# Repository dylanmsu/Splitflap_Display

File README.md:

# Splitflap_Display
software to digtally drive a public splitflap display using arduino. The display is meant do be deployed in a steamtrain station where it reads the data from their server.
This project is still in development and requires major improvements and code cleanup.

## this repository contains:
* arduino library
* kicad schematic and pcb desgin
* basic documentation about the splitflap display modules

## The Arduino compatible Library
The included Arduino compatible library is designed to drive a complete split flap display board with 32 individual modules. There are also methods included to drive the individual split flaps with great control. You can for example call the method:
```c++
splitflaps.flipSegment(int segment);
```
That line of code will flip the segment once. Or if you want more control, there is the method: 
```c++
splitflaps.writeSegment(int segment, int state);
```
It sets the state of the selected h-Bridge. There are (in the future) a bunch of example sketches with different use cases for the library. However, they all require at least one driver PCB to actually drive the split flap modules.

## The driver PCB
The driver PCBs can drive 8 splitflap modules at the same time, for that it uses 4 SN754410NE chips (L293D in version 4) that are driven by two 74HC595 shift registers. One shift registers drives the H-bridges, the other enables the outputs of the 8 H-Bridges so they dont waste unnecessary power. The communication protocol is quite simple. You have two serial data inputs in the input connector, one is to enable the individual H-Bridges (DiE, ClkE, LaE), the other is to drive the individual H-bridges (Di, Clk, La). They can be daisy-chained to drive an infinite number of splitflap modules. <br> To actually drive splitflap modules with it, open the arduino sketch named TestDriver. Connect the splitflap modules solenoid connections to the H-Bridge output pairs. Then connect the serial pins to the arduino pins listed in the sketch. and lastly connect 20v to the Vdd input connector. Upload the sketch, the splitflaps should be working.

* V1: first version, fully made in kicad with through hole components
* V4: latest version, made in EasyEDA with mostly SMD components

## authors
* Dylan Missuwe
* Tijl Desmet

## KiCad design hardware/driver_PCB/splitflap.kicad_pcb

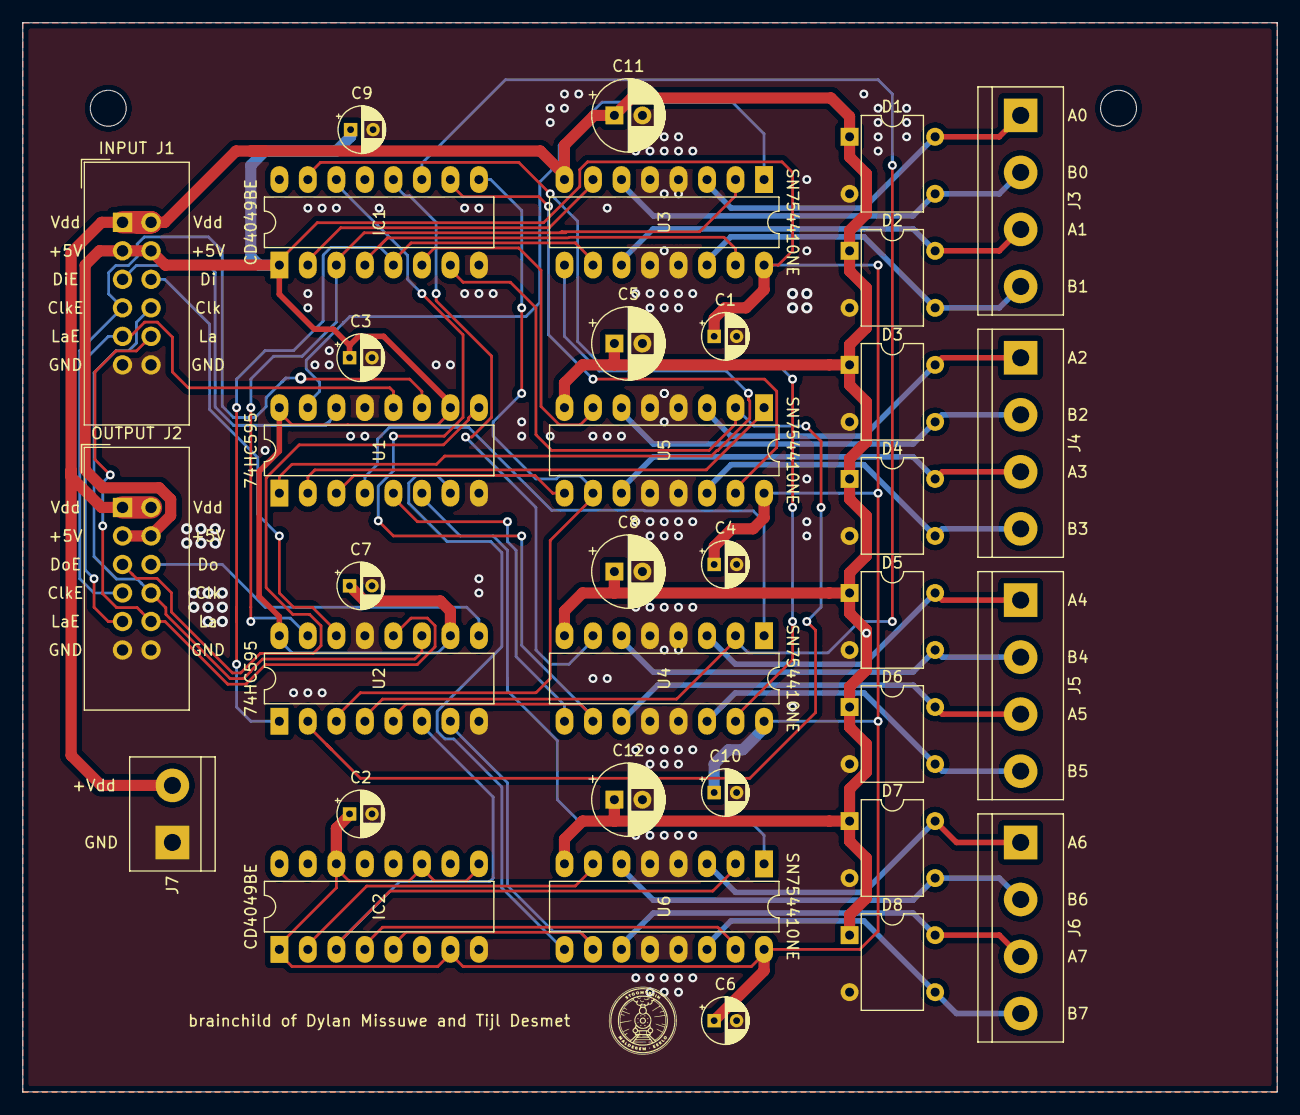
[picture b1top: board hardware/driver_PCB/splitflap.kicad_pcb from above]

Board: 2 copper layers, 111.8 x 95.2 mm, 35 parts (0 on the bottom side), 51 nets.

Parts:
C1, C2, C3, C4, C6, C7, C9, C10: CP; CP_Radial_D4.0mm_P2.00mm
C5, C8, C11, C12: CP; CP_Radial_D6.3mm_P2.50mm
D1, D2, D3, D4, D5, D6, D7, D8: D_Bridge_+-AA; Diode_Bridge_DIP-4_W7.62mm_P5.08mm
IC1, IC2: CD4049UBE; DIP-16_W7.62mm_LongPads
INPUT J1: Conn_02x06_Odd_Even; IDC-Header_2x06_P2.54mm_Vertical
J3, J4, J5, J6: Screw_Terminal_01x04; TerminalBlock_bornier-4_P5.08mm
J7: Screw_Terminal_01x02; TerminalBlock_bornier-2_P5.08mm
OUTPUT J2: Conn_02x06_Odd_Even; IDC-Header_2x06_P2.54mm_Vertical
U1, U2: 74HC595; DIP-16_W7.62mm_LongPads
U3, U4, U5, U6: SN754410NE; DIP-16_W7.62mm_LongPads

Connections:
GND: C1.2, C2.2, C3.2, C4.2, C5.2, C6.2, C7.2, C8.2, C9.2, C10.2, C11.2, C12.2, D1.2, D2.2, D3.2, D4.2, D5.2, D6.2, D7.2, D8.2, IC1.8, IC2.8, INPUT J1.11, INPUT J1.12, J7.1, OUTPUT J2.11, OUTPUT J2.12, U1.8, U1.13, U2.8, U2.13, U3.4, U3.5, U3.12, U3.13, U4.4, U4.5, U4.12, U4.13, U5.4, U5.5, U5.12, U5.13, U6.4, U6.5, U6.12, U6.13
unnamed: D1.3, J3.2, U3.6
unnamed: D1.4, J3.1, U3.3
unnamed: D2.3, J3.4, U3.14
unnamed: D2.4, J3.3, U3.11
unnamed: D3.3, J4.2, U5.6
unnamed: D3.4, J4.1, U5.3
unnamed: D4.3, J4.4, U5.14
unnamed: D4.4, J4.3, U5.11
unnamed: D5.3, J5.2, U4.6
unnamed: D5.4, J5.1, U4.3
unnamed: D6.3, J5.4, U4.14
unnamed: D6.4, J5.3, U4.11
unnamed: D7.3, J6.2, U6.6
unnamed: D7.4, J6.1, U6.3
unnamed: D8.3, J6.4, U6.14
unnamed: D8.4, J6.3, U6.11
unnamed: IC1.2, U3.7
unnamed: IC1.3, U2.15, U3.2
unnamed: IC1.4, U3.15
unnamed: IC1.5, U2.1, U3.10
unnamed: IC1.6, U5.7
unnamed: IC1.7, U2.2, U5.2
unnamed: IC1.9, U2.3, U5.10
unnamed: IC1.10, U5.15
unnamed: IC1.11, U2.4, U4.2
unnamed: IC1.12, U4.7
unnamed: IC1.14, U2.5, U4.10
unnamed: IC1.15, U4.15
unnamed: IC2.2, U6.7
unnamed: IC2.3, U2.6, U6.2
unnamed: IC2.4, U6.15
unnamed: IC2.5, U2.7, U6.10
unnamed: INPUT J1.5, U1.14
unnamed: INPUT J1.6, U2.14
unnamed: INPUT J1.7, OUTPUT J2.7, U1.11
unnamed: INPUT J1.8, OUTPUT J2.8, U2.11
unnamed: INPUT J1.9, OUTPUT J2.9, U1.12
unnamed: INPUT J1.10, OUTPUT J2.10, U2.12
unnamed: OUTPUT J2.5, U1.9
unnamed: OUTPUT J2.6, U2.9
unnamed: U1.1, U3.9
unnamed: U1.2, U5.1
unnamed: U1.3, U5.9
unnamed: U1.4, U4.1
unnamed: U1.5, U4.9
unnamed: U1.6, U6.1
unnamed: U1.7, U6.9
unnamed: U1.15, U3.1
VCC: C1.1, C2.1, C3.1, C4.1, C6.1, C7.1, C9.1, C10.1, IC1.1, IC2.1, IC2.7, IC2.9, IC2.11, IC2.14, INPUT J1.3, INPUT J1.4, OUTPUT J2.3, OUTPUT J2.4, U1.10, U1.16, U2.10, U2.16, U3.16, U4.16, U5.16, U6.16
VDD: C5.1, C8.1, C11.1, C12.1, D1.1, D2.1, D3.1, D4.1, D5.1, D6.1, D7.1, D8.1, INPUT J1.1, INPUT J1.2, J7.2, OUTPUT J2.1, OUTPUT J2.2, U3.8, U4.8, U5.8, U6.8

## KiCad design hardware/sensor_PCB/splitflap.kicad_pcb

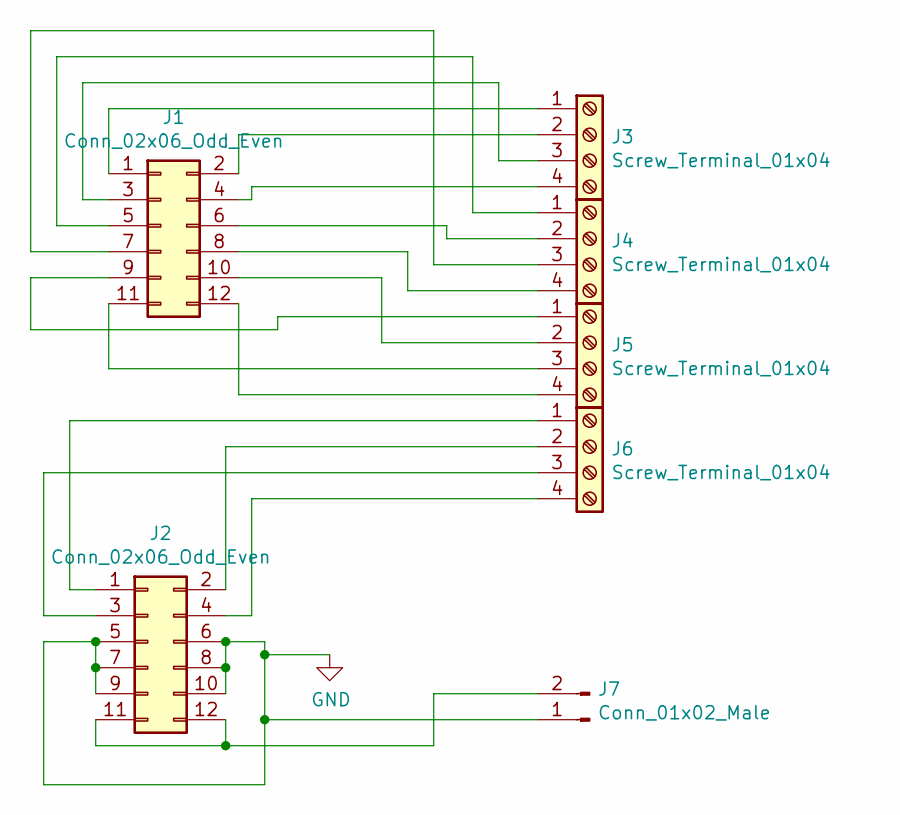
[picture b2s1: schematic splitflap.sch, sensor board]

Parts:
J1, J2: Conn_02x06_Odd_Even; IDC-Header_2x06_P2.54mm_Vertical
J3, J4, J5, J6: Screw_Terminal_01x04; TerminalBlock_bornier-4_P5.08mm
J7: Conn_01x02_Male; JST_EH_B2B-EH-A_1x02_P2.50mm_Vertical

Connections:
GND: J2.5, J2.6, J2.7, J2.8, J2.9, J2.10, J7.1
unnamed: J1.1, J3.1
unnamed: J1.2, J3.2
unnamed: J1.3, J3.3
unnamed: J1.4, J3.4
unnamed: J1.5, J4.1
unnamed: J1.6, J4.2
unnamed: J1.7, J4.3
unnamed: J1.8, J4.4
unnamed: J1.9, J5.1
unnamed: J1.10, J5.2
unnamed: J1.11, J5.3
unnamed: J1.12, J5.4
unnamed: J2.1, J6.1
unnamed: J2.2, J6.2
unnamed: J2.3, J6.3
unnamed: J2.4, J6.4
unnamed: J2.11, J2.12, J7.2

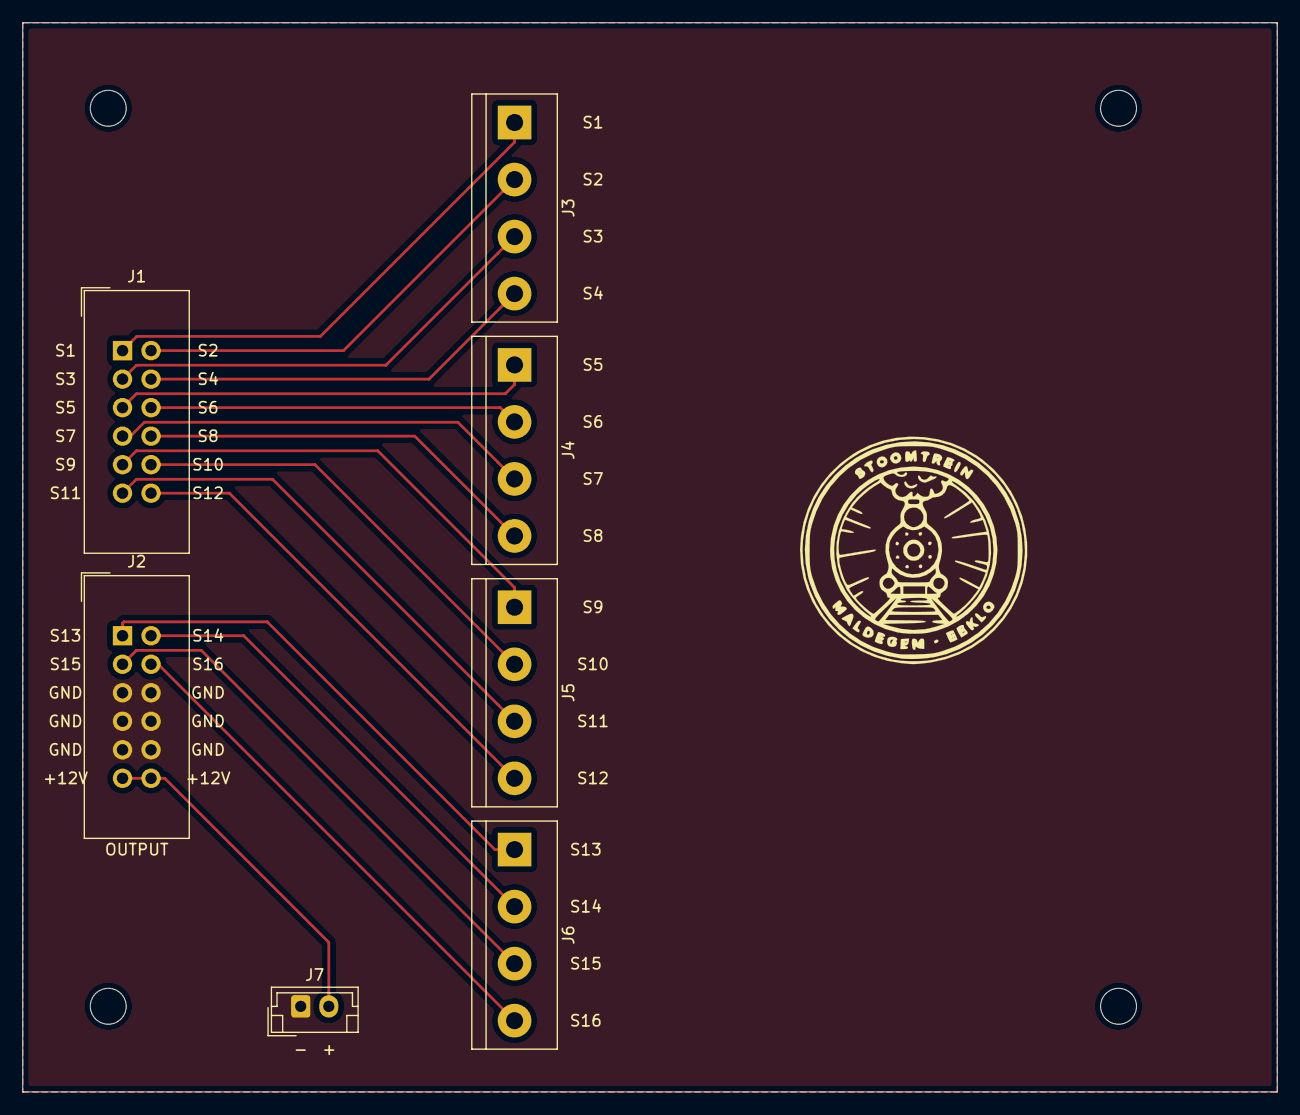
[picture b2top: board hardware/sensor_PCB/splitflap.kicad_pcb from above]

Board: 2 copper layers, 111.8 x 95.2 mm, 7 parts (0 on the bottom side), 18 nets.

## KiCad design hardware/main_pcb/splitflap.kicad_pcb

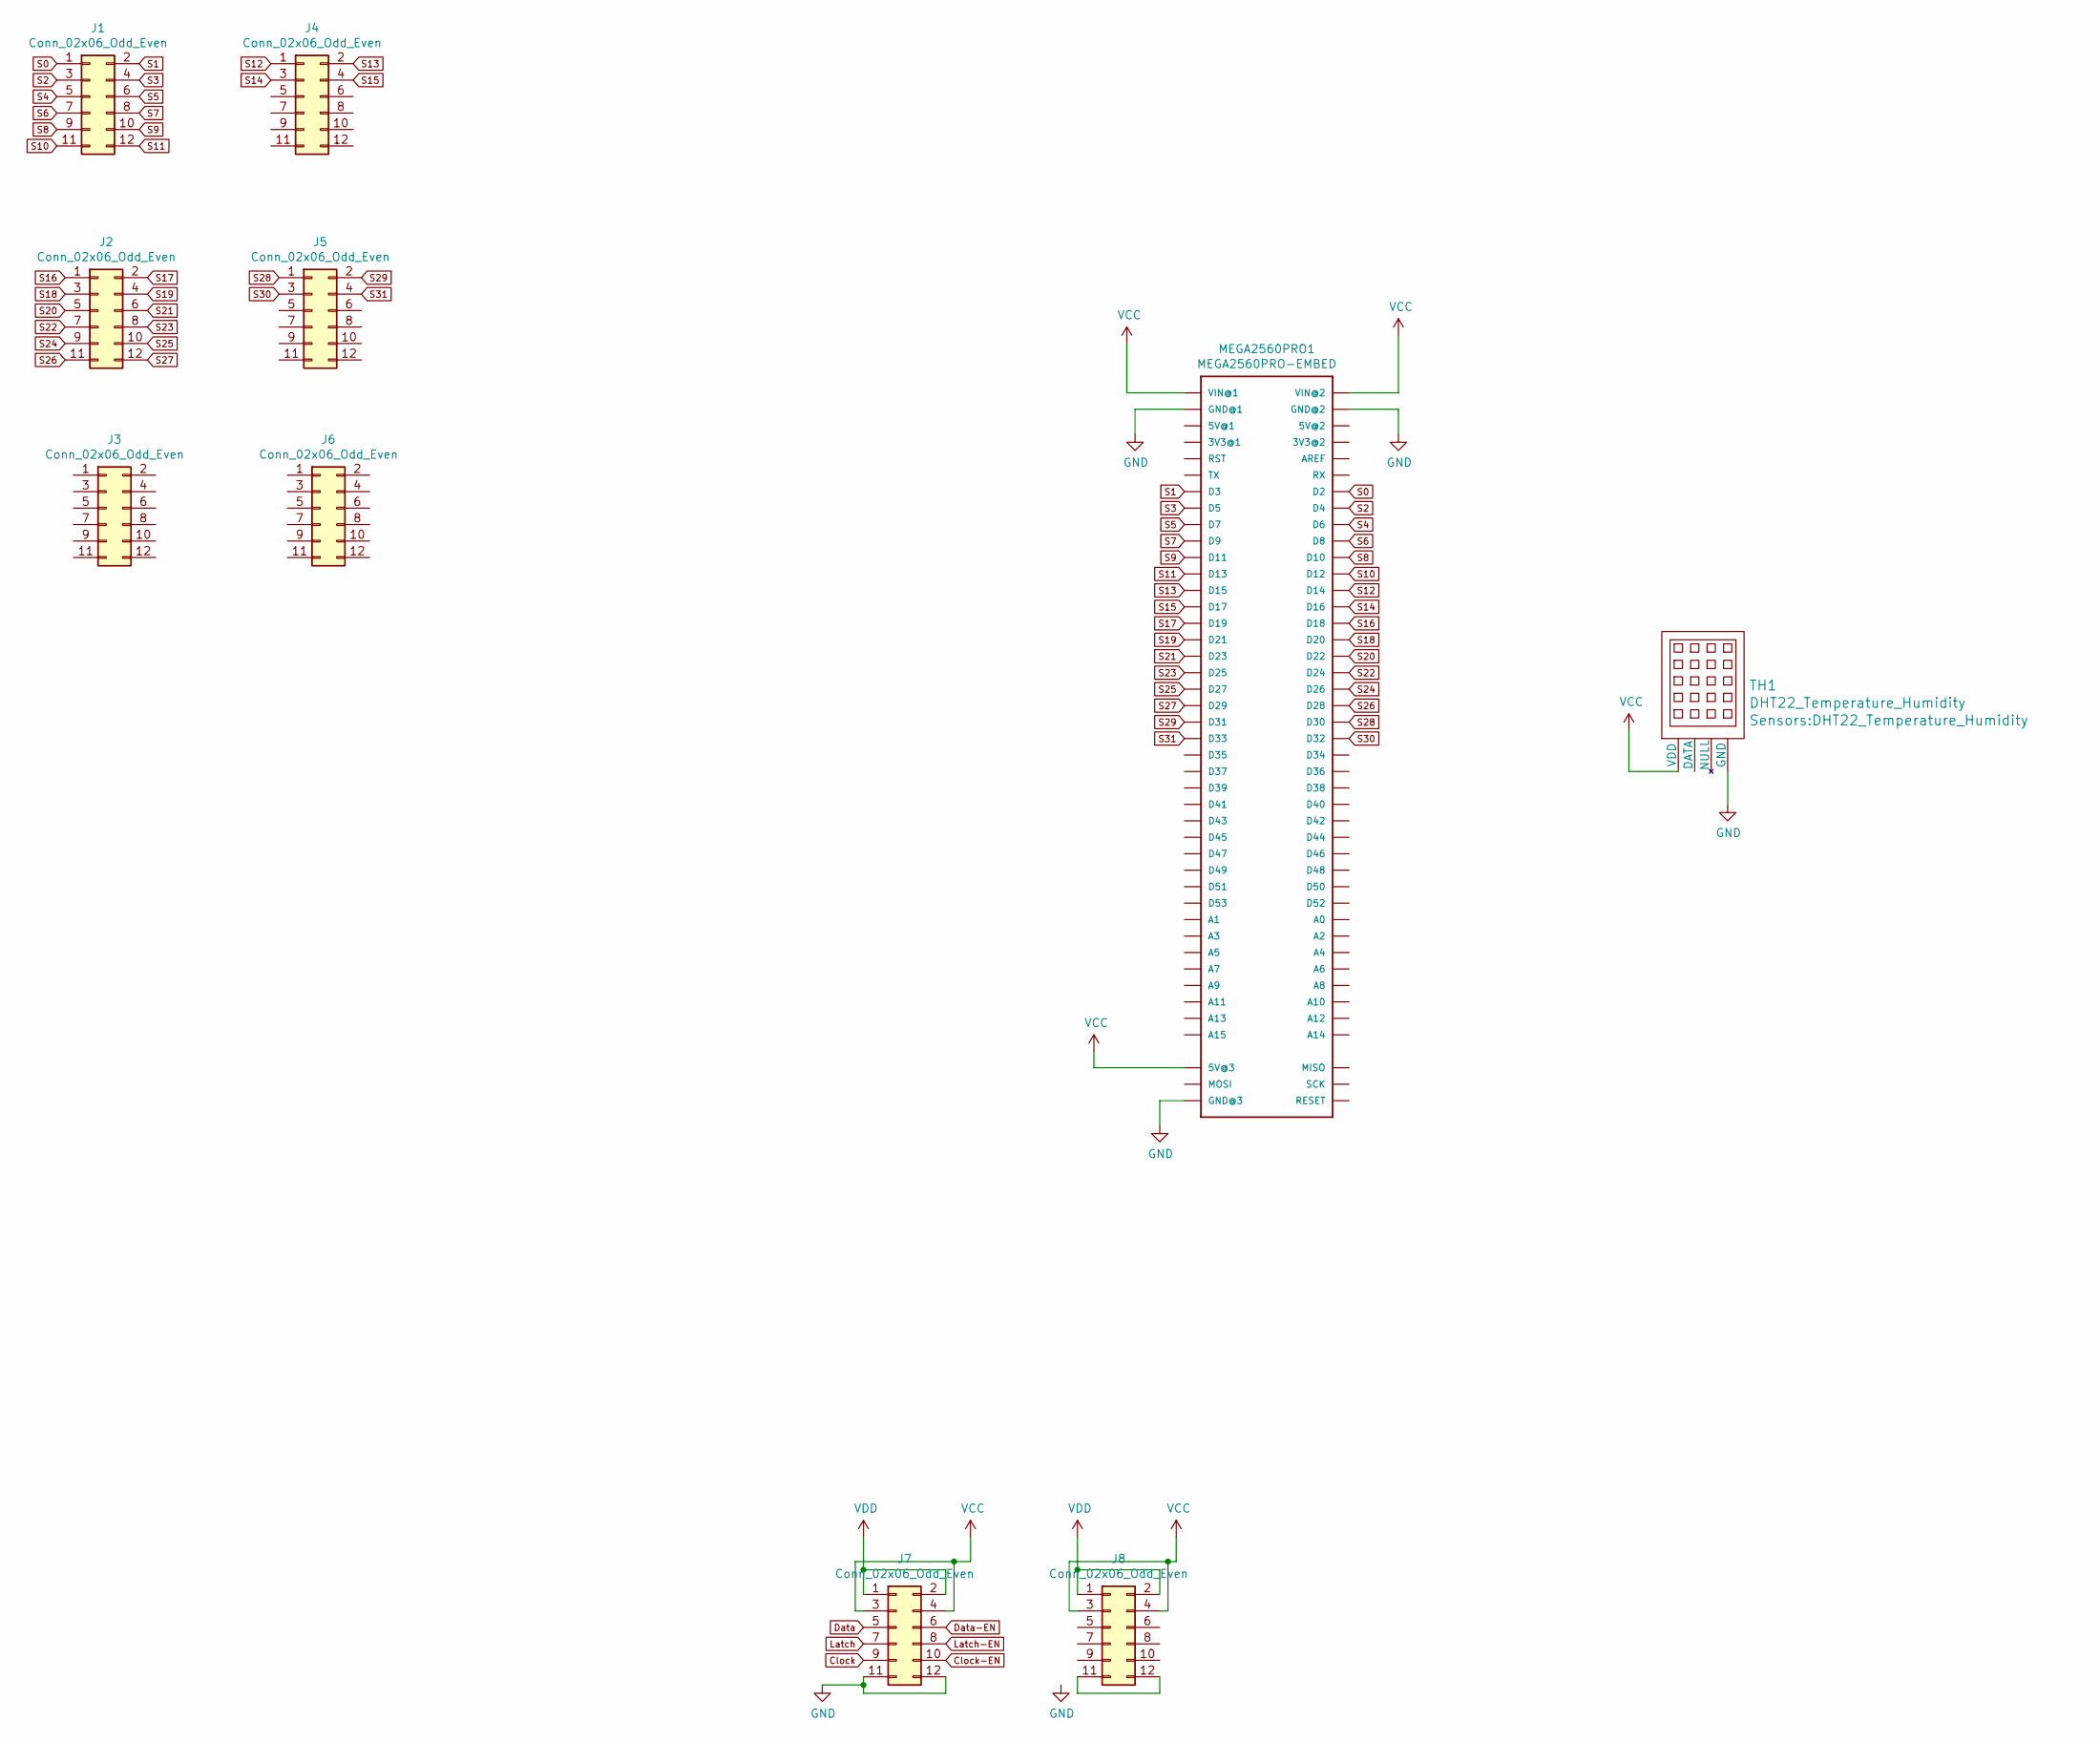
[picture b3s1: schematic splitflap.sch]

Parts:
J1, J2, J3, J4, J5, J6, J7, J8: Conn_02x06_Odd_Even; IDC-Header_2x06_P2.54mm_Vertical
MEGA2560PRO1: MEGA2560PRO-EMBED
TH1: DHT22_Temperature_Humidity

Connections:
Clock: J7.9
Clock-EN: J7.10
Data: J7.5
Data-EN: J7.6
GND: J7.11, J7.12, MEGA2560PRO1.GND@1, MEGA2560PRO1.GND@2, MEGA2560PRO1.GND@3, TH1.4 (GND)
Latch: J7.7
Latch-EN: J7.8
unnamed: J8.11, J8.12
S0: J1.1, MEGA2560PRO1.D2
S1: J1.2, MEGA2560PRO1.D3
S2: J1.3, MEGA2560PRO1.D4
S3: J1.4, MEGA2560PRO1.D5
S4: J1.5, MEGA2560PRO1.D6
S5: J1.6, MEGA2560PRO1.D7
S6: J1.7, MEGA2560PRO1.D8
S7: J1.8, MEGA2560PRO1.D9
S8: J1.9, MEGA2560PRO1.D10
S9: J1.10, MEGA2560PRO1.D11
S10: J1.11, MEGA2560PRO1.D12
S11: J1.12, MEGA2560PRO1.D13
S12: J4.1, MEGA2560PRO1.D14
S13: J4.2, MEGA2560PRO1.D15
S14: J4.3, MEGA2560PRO1.D16
S15: J4.4, MEGA2560PRO1.D17
S16: J2.1, MEGA2560PRO1.D18
S17: J2.2, MEGA2560PRO1.D19
S18: J2.3, MEGA2560PRO1.D20
S19: J2.4, MEGA2560PRO1.D21
S20: J2.5, MEGA2560PRO1.D22
S21: J2.6, MEGA2560PRO1.D23
S22: J2.7, MEGA2560PRO1.D24
S23: J2.8, MEGA2560PRO1.D25
S24: J2.9, MEGA2560PRO1.D26
S25: J2.10, MEGA2560PRO1.D27
S26: J2.11, MEGA2560PRO1.D28
S27: J2.12, MEGA2560PRO1.D29
S28: J5.1, MEGA2560PRO1.D30
S29: J5.2, MEGA2560PRO1.D31
S30: J5.3, MEGA2560PRO1.D32
S31: J5.4, MEGA2560PRO1.D33
VCC: J7.3, J7.4, J8.3, J8.4, MEGA2560PRO1.5V@3, MEGA2560PRO1.VIN@1, MEGA2560PRO1.VIN@2, TH1.1 (VDD)
VDD: J7.1, J7.2, J8.1, J8.2

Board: 2 copper layers, 10 parts (0 on the bottom side), 36 nets, no tracks yet.

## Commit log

2019-11-01 created arduino file
2019-11-01 added some untested code
2019-11-01 updated the 'drawChar' function
2019-11-02 made code more modular
2019-11-02 added some functionality
2019-11-03 got the code to print 'hello' on actual hardware
2019-11-03 improved efficiency
2019-11-04 Character test
2019-11-04 improved array handling
2019-11-04 created a function whitch converts a string to an index array
2019-11-04 finished array conversion function
2019-11-04 some updates
2019-11-05 got strings fully working
2019-11-05 string handling from serial input
2019-11-05 multi dysplay experimenting
2019-11-06 experimenting with red text
2019-11-07 Drank some cola
2019-11-08 code works on multiple displays now
2019-11-08 Pokémon Gooooo
2019-11-09 update communication
2019-11-09 added sensor functionality
2019-11-10 uygvou
2019-11-10 now able to zero multiple displays at once
2019-11-10 MYSQL communication for peripherals added
2019-11-10 Serial disabled
2019-11-10 debugging
2019-11-10 Base version
2019-11-10 got red text working
2019-11-10 Minor Changes
2019-11-11 Added LED functionality
2019-11-12 Added Wifi functionality in database
2019-11-12 Added WiFi functionality and minor updates
2019-11-21 Update MySQL
2019-11-21 got 8 charakter text working
2019-12-06 added kicad schematic
2019-12-07 updated kicad schematic
2019-12-07 updated pcb layout
2020-01-23 finished pcb layout
2020-02-22 changed pcb layout and interface
2020-02-23 added functionality to read from serial
2020-02-24 some code cleanup
2020-03-10 updated pcb
2020-04-07 converted arduino sketch to a library ann pcb updates
2020-04-07 added some examples to the library
2020-04-10 updated splitflap library
2020-04-12 Update today
2020-05-28 merge
2020-05-28 Dylan wist het niet meer
2020-07-17 implemented ethernet client
2020-09-27 made code more efficient and modular
2020-11-03 added PCB layout
2020-11-03 Hardware
2020-11-05 Changes to character list
2020-11-05 General changes for mental wellbeing
2020-11-05 Added Documentation
2020-11-17 added hours and minues
2021-01-03 added drivertest example
2021-01-03 remove .vscode
2021-01-03 moved charakter list to documentation
2021-01-04 cleanup
2021-01-04 Create LICENSE
2021-01-26 can now send headers with information to api
2021-01-27 code update
2021-01-27 added config file
2021-02-18 now makes more efficient use of the splitflap modules
2021-03-07 made code work again
